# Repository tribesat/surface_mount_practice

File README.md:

# Surface Mount Practice

This board is designed to teach surface mount soldering. The circuit is an [astable multivibrator](https://en.wikipedia.org/wiki/Multivibrator#Astable_multivibrator) that blinks the two LEDs. It was designed to be easy to assemble, and show clearly if it is working correctly or not.

This board was designed for use at the College of William and Mary's Small Hall Makerspace.

<a href="https://oshpark.com/shared_projects/60MGKlDe"></img></a>

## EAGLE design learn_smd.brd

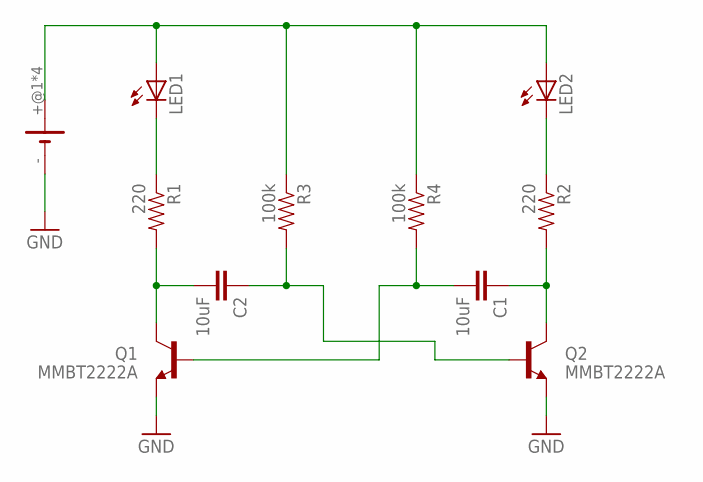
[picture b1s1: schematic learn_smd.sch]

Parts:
BT1: BAT-HLD-001-THM; LINX_BAT-HLD-001-THM
C1, C2: 10uF; 0805
LED1, LED2: LEDCHIP-LED0805; CHIP-LED0805
Q1, Q2: MMBT2222A; SOT23-3
R1, R2: 220; 0805
R3, R4: 100k; 0805

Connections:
GND: BT1.-, Q1.2 (E), Q2.2 (E)
unnamed: LED1.C, R1.1
unnamed: C2.2, Q1.3 (C), R1.2
unnamed: C1.2, Q1.1 (B), R4.2
unnamed: C1.1, Q2.3 (C), R2.2
unnamed: LED2.C, R2.1
unnamed: BT1.+@1 (+), BT1.+@2 (+), BT1.+@3 (+), BT1.+@4 (+), LED1.A, LED2.A, R3.1, R4.1
unnamed: C2.1, Q2.1 (B), R3.2

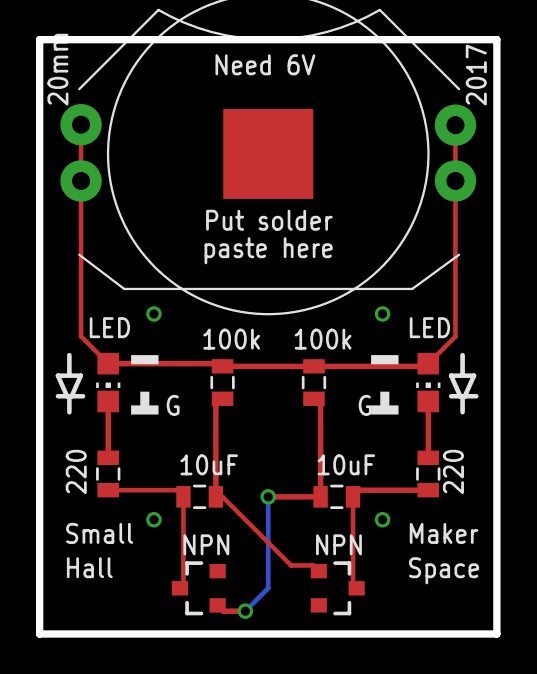
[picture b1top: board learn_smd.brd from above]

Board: 2 copper layers, 25.4 x 33.0 mm, 11 parts (0 on the bottom side), 8 nets.

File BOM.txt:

component/value, size, quanity, digikey part number
--------------------------------------------------------
Red led, 0805, 2, 160-1469-2-ND
100k resistor, 0805, 2, 311-100KCRCT-ND
220 resistor, 0805, 2, 311-220CRCT-ND
10uF capacitor, 0805, 2, 490-3340-1-ND
NPN transistor, SOT-23, 2, MMBT2222ALT1GOSCT-ND
Curved Battery Holder, 20mm, 1, BAT-HLD-001-THM

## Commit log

2017-02-05 eagle files
2017-02-06 added BOM
2017-02-14 updated silk
2017-02-14 switched to through hole battery
2017-02-14 resized board
2017-02-14 increase battery overhang
2017-02-14 made board smaller
2017-02-14 final changes for fab
2017-02-14 fixed BOM errror
2017-02-28 fixes #3
    connects top and bottom grounding
2017-03-14 renamed tranistor to npn on silk
2017-03-22 added g to represnt where green line is
2017-03-28 final changer for order
2017-04-27 added oshpark order button
2017-10-27 Updated readme
    add link to information about astable multivibrator

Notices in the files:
parts and their libraries:
SparkFun-Capacitors: Licensing: Creative Commons ShareAlike 4.0 International - https://creativecommons.org/licenses/by-sa/4.0
